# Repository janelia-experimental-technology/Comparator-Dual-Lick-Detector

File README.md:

# Comparator Dual Lick Detector
Mouse lick detector 

https://doi.org/10.25378/janelia.29685659

Summary

Lick sensors can be important tools in determining licking and drinking behavior of rodents during behavioral and neuroscience research. Commercially available lick sensors generally utilize either electrical, optical or force sensors in measuring licking and drinking behavior. A common problem with commercially available lick sensors is the production of significant electrical artifacts during recording of neural signals.

To measure neural signals without the production of electrical artifacts, researchers at Howard Hughes Medical Institute’s Janelia Research Campus have developed a Comparator Dual Lick Port Detector. The detector is designed to monitor a contact-type lick port without generating electrical interference on neural signals, to minimize sensation to subject animals and to allow fast detection of neural signals. The developed system modulates a signal at the lick port and analyzes the signal for changes due to attenuation (resistance change) or phase (due to capacitive change).

In “A low-cost solution to measure mouse licking in an electrophysiological setup with a standard analog-to-digital” by Abdallah Hayar, Jeri L. Bryant, John D. Boughter, and Detlef H. Heck in J Neurosci Methods (2006 June 15), a lick detection method is described that measures the potential difference caused by a rodent lick on a metal lick port using an analog-to-digital converter (ADC). The detection was robust and did not create artifacts in electrophysiological recordings. This method was tested at Janelia and found to work well. This novel system was designed to make the design cheaper and self-contained. An adjustable threshold comparator was substituted for the ADC and the circuit was opto-isolated.
Benefit

    Monitors a contact-type lick port without generating electrical interference on neural signals
    Enables fast detection time of less than one millisecond
    Minimizes sensations to subject animals thereby improving signal monitoring

Market Application

    Behavioral monitoring in animal research studies
    Animal research studies related primarily to neuronal circuit research

This design detects lick port licks using a method from:

A low-cost solution to measure mouse licking in an
electrophysiological setup with a standard analog-to-digital
converter

Abdallah Hayar, Jeri L. Bryant, John D. Boughter, and Detlef H. Heck*

A comparator is used in lieu of the ADC to create a simple circuit that outputs TTL levels.

The circuit can be built with or without electrical isolation.

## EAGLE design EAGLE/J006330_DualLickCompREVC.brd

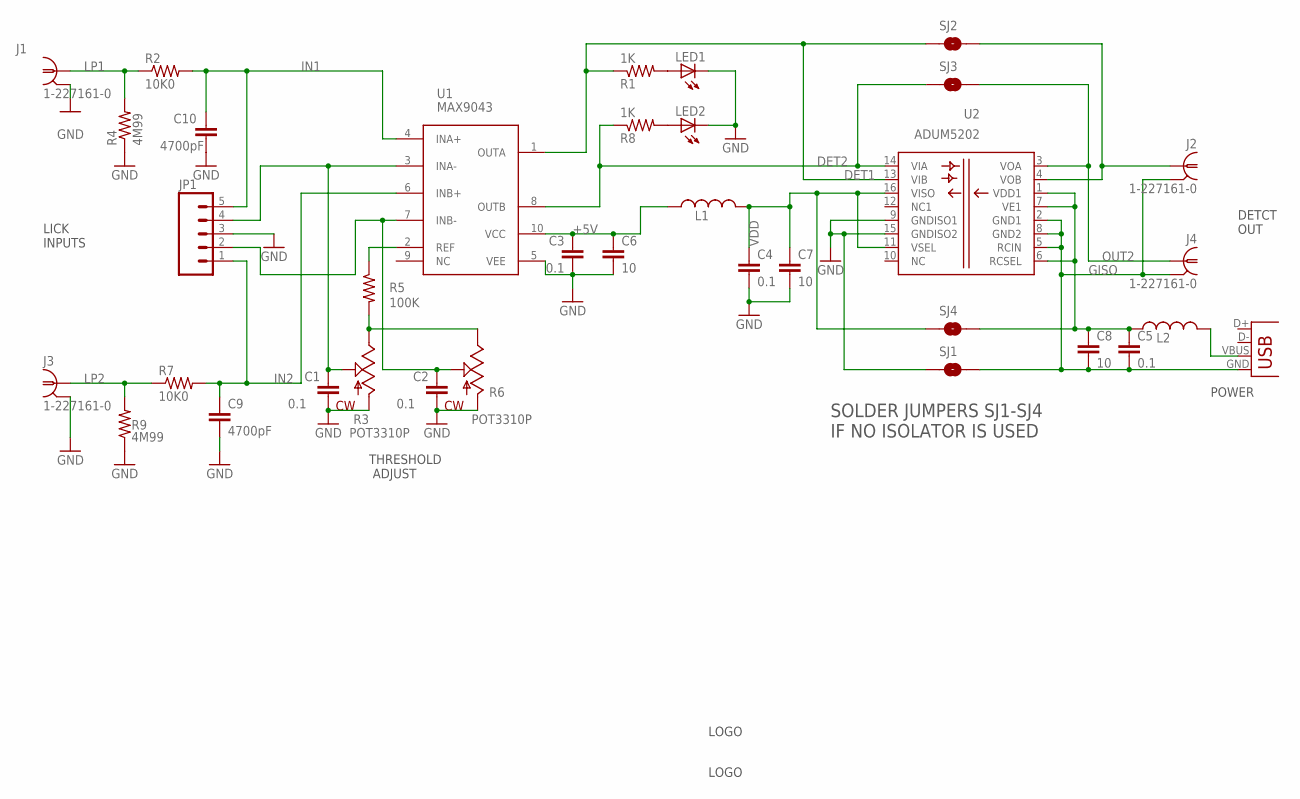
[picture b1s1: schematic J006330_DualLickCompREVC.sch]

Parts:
C1, C2, C3, C4, C5: 0.1; 0603S
C6, C7, C8: 10; 0805S
C9, C10: 4700pF; 0805S
J1, J2, J3, J4: 1-227161-0; AMP_227161
J100: USB; 10118194
JP1: M05LOCK; 1X05_LOCK
L1, L2: INDUCTOR_SM0805S; 0805S
LED1, LED2: LED5MM
R1, R8: 1K; 0805S
R2, R7: 10K0; 0805S
R3, R6: POT3310P; 3310P
R4, R9: 4M99; 0805S
R5: 100K; 0805S
SJ1, SJ2, SJ3, SJ4: SOLDERJUMPERNO; SJ_2S-NO
U1: MAX9043; UMAX10
U2: ADUM5202; SO-16-7.5MM
U$1: JFRC-LOGOLOGO_OP; LOGO_BMP_OP
U$2: JFRC-LOGOLOGO_JANELIA_2014_ECLOSURE; LOGO_JANELIA_2014_ENCLOSURE

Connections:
+5V: C3.1, C6.1, L1.1, U1.10 (VCC)
DET1: R1.1, SJ2.1, U1.1 (OUTA), U2.13 (VIB)
DET2: R8.1, SJ3.1, U1.8 (OUTB), U2.14 (VIA)
GISO: C5.2, C8.2, J2.2, J4.2, J100.GND, SJ1.2, U2.2 (GND1), U2.5 (RCIN), U2.8 (GND2)
GND: C1.2, C2.2, C3.2, C4.2, C6.2, C7.2, C9.2, C10.2, J1.2, J3.2, JP1.3, LED1.K (C), LED2.K (C), R3.1 (CCW), R4.1, R6.1 (CCW), R9.1, SJ1.1, U1.5 (VEE), U2.9 (GNDISO1), U2.15 (GNDISO2)
IN1: C10.1, JP1.5, R2.2, U1.4 (INA+)
IN2: C9.1, JP1.1, R7.2, U1.6 (INB+)
LP1: J1.1, R2.1, R4.2
LP2: J3.1, R7.1, R9.2
unnamed: J2.1, SJ2.2, U2.4 (VOB)
unnamed: LED1.A, R1.2
unnamed: R5.1, U1.2 (REF)
unnamed: R3.3 (CW), R5.2, R6.3 (CW)
unnamed: C1.1, JP1.4, R3.2 (W), U1.3 (INA-)
unnamed: LED2.A, R8.2
unnamed: J100.VBUS, L2.2
unnamed: C2.1, JP1.2, R6.2 (W), U1.7 (INB-)
OUT2: J4.1, SJ3.2, U2.3 (VOA)
VDD: C4.1, C7.1, L1.2, SJ4.1, U2.11 (VSEL), U2.16 (VISO)
VIN: C5.1, C8.1, L2.1, SJ4.2, U2.1 (VDD1), U2.6 (RCSEL), U2.7 (VE1)

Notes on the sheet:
LICK INPUTS
DETCT OUT
POWER
THRESHOLD ADJUST
SOLDER JUMPERS SJ1-SJ4 IF NO ISOLATOR IS USED

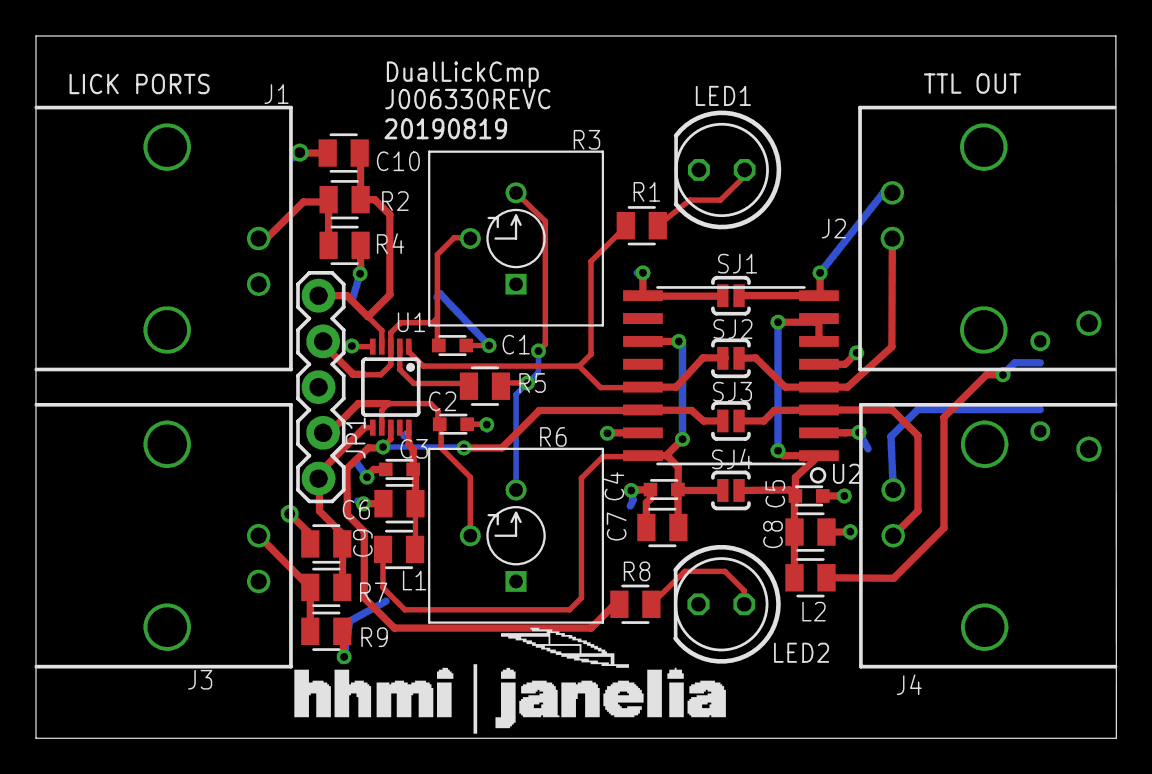
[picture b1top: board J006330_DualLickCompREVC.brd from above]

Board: 2 copper layers, 60.0 x 39.0 mm, 37 parts (1 on the bottom side), 20 nets.

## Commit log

2026-05-18 update readme and add license file
2026-06-15 add DOI

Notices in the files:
parts and their libraries:
SparkFun: Licensing: CC v3.0 Share-Alike You are welcome to use this library for commercial purposes.
